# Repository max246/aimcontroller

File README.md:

# Playstation Aim Controller 

Hack of the Playstation aim controller

I have re-wired the controller into a Teensy 3.6 to "filter the commands" and potentially create a combination to help or cheat in games. 
The idea was to understand how it would be possible to do it and there was no intetion to allow easy cheat in games.

Using 3 digital potentiometer allowed me to even read the analog inputs and reprodue them from the micro controller.

There were extra 6 buttons to activate other feature that could be implemented.

The source code provide only the functionality of COPY but a Burst or other combination can be developed.

The power supply was connected directly to the main battery and the controller would have a main switch to deactivate it, unfortunatly the MCP will not keep the last output, therefore I suggest to turn off the remote first then the Teensy.

The re-wiring took a lot of time and I suggest to get a very good pair of tweezer to pull them around the controller, blue tac is very handy to stick them down while working on the right length of wires!

## PCB

Connector to solder on the PCB is a TE Connectivity FPC 0.5mm Pitch 24 Way Straight SMT Female FPC Connector. 
Part number: 2-1734742-4

RS components https://uk.rs-online.com/web/p/fpc-connectors/9097441

The ribbon cable is a 24 Pins AWM 2896 VW-1 30V 80C, which you can source on aliexpress or by buying  a broken or cheap second aim controller ( the path I followed ).

## Reverse Engineering

I have worked out each pins what they do, but please double check the orientation before connecting everything, it will be easy as the ground pins are close by and checking from the bespoke PCB to the actually Playstation board will take few seconds.

I have made a small PDF with the schematic of what I found out ( [LINK](https://raw.githubusercontent.com/max246/aimcontroller/master/PS4%20Aim%20Controller.pdf)
 ) .

R2 an L2 are not clever re-created, just a hack I found that worked, they apparently have a "pull up" resistor of X ohm and the pressure change the voltage difference. 
I have used a digital potentiometer to short the Spare R2/L2 to the R2/L2 to create the similar beahvour. It worked!

Joystick Front ( Left ) and Joystick Back ( Right ) were easy to work it out, and wired up with a digital potentiometer.

The chip I have used is MCP4251-104E/P 100k Ohm from RS ( https://uk.rs-online.com/web/p/digital-potentiometers/7239731/ )

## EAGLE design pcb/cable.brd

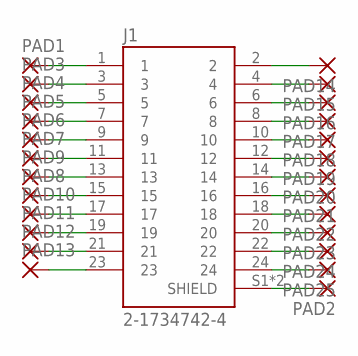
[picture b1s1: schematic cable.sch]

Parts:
J1: 2-1734742-4; TE_2-1734742-4
PAD1, PAD2, PAD3, PAD4, PAD5, PAD6, PAD7, PAD8, PAD9, PAD10, PAD11, PAD12, PAD13, PAD14, PAD15, PAD16, PAD17, PAD18, PAD19, PAD20, PAD21, PAD22, PAD23, PAD24, PAD25: SMD2; SMD1,27-2,54

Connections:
unnamed: J1.2, PAD14.1
unnamed: J1.4, PAD15.1
unnamed: J1.6, PAD16.1
unnamed: J1.8, PAD17.1
unnamed: J1.10, PAD18.1
unnamed: J1.12, PAD19.1
unnamed: J1.14, PAD20.1
unnamed: J1.16, PAD21.1
unnamed: J1.18, PAD22.1
unnamed: J1.20, PAD23.1
unnamed: J1.22, PAD24.1
unnamed: J1.24, PAD25.1
unnamed: J1.1, PAD1.1
unnamed: J1.3, PAD3.1
unnamed: J1.5, PAD4.1
unnamed: J1.7, PAD5.1
unnamed: J1.9, PAD6.1
unnamed: J1.11, PAD7.1
unnamed: J1.13, PAD9.1
unnamed: J1.15, PAD8.1
unnamed: J1.17, PAD10.1
unnamed: J1.19, PAD11.1
unnamed: J1.21, PAD12.1
unnamed: J1.23, PAD13.1
unnamed: J1.S1 (SHIELD), J1.S2 (SHIELD), PAD2.1

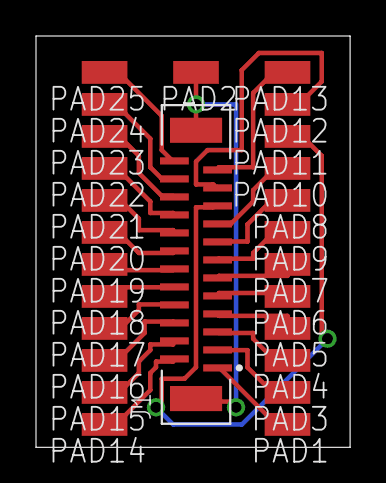
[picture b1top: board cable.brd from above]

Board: 2 copper layers, 17.4 x 22.9 mm, 26 parts (0 on the bottom side), 25 nets.

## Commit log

2019-02-04 add fils
